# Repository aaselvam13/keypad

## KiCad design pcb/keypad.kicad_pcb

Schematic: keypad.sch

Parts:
C1, C2: 22pF; C_0805_2012Metric
C3, C4, C5: 0.1uF; C_0805_2012Metric
C6: 10uF; C_0805_2012Metric
C7: 1uF; C_0805_2012Metric
D1, D2, D3, D4, D5, D6: D_Small; D_SOD-123
F1: 500mA; Fuse_1206_3216Metric
MX1, MX2, MX3, MX4, MX5, MX6: MX-NoLED; MXOnly-1U-Hotswap
R1, R2: 22; R_0805_2012Metric
R3: 10k; R_0805_2012Metric
SW1: SW_Push; SKQG-1155865
U1: ATmega32U4-AU; TQFP-44_10x10mm_P0.8mm
USB1: Molex-0548190589
Y1: 16MHz; Crystal_SMD_3225-4Pin_3.2x2.5mm

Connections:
+5V: C3.1, C4.1, C5.1, C6.1, F1.1, U1.2 (UVCC), U1.7 (VBUS), U1.14 (VCC), U1.24 (AVCC), U1.34 (VCC), U1.44 (AVCC)
COL0: MX1.1 (COL), MX2.1 (COL), U1.29 (PB5)
COL1: MX3.1 (COL), MX4.1 (COL), U1.28 (PB4)
COL2: MX5.1 (COL), MX6.1 (COL), U1.26 (PD6)
D+: R2.2, USB1.3 (D+)
D-: R1.2, USB1.4 (D-)
GND: C1.2, C2.2, C3.2, C4.2, C5.2, C6.2, C7.2, R3.1, SW1.1, U1.5 (UGND), U1.15 (GND), U1.23 (GND), U1.35 (GND), U1.43 (GND), USB1.1 (GND), Y1.2, Y1.4
unnamed: C1.1, U1.16 (XTAL2), Y1.3
unnamed: C2.1, U1.17 (XTAL1), Y1.1
unnamed: C7.1, U1.6 (UCAP)
unnamed: D1.2, MX1.2 (ROW)
unnamed: D2.2, MX2.2 (ROW)
unnamed: D3.2, MX3.2 (ROW)
unnamed: D4.2, MX4.2 (ROW)
unnamed: D5.2, MX5.2 (ROW)
unnamed: D6.2, MX6.2 (ROW)
unnamed: R1.1, U1.3 (D-)
unnamed: R2.1, U1.4 (D+)
unnamed: R3.2, U1.33 (~HWB~/PE2)
unnamed: SW1.2, U1.13 (~RESET)
ROW0: D1.1, D3.1, D5.1, U1.27 (PD7)
ROW1: D2.1, D4.1, D6.1, U1.30 (PB6)
VCC: F1.2, USB1.5 (VBUS)

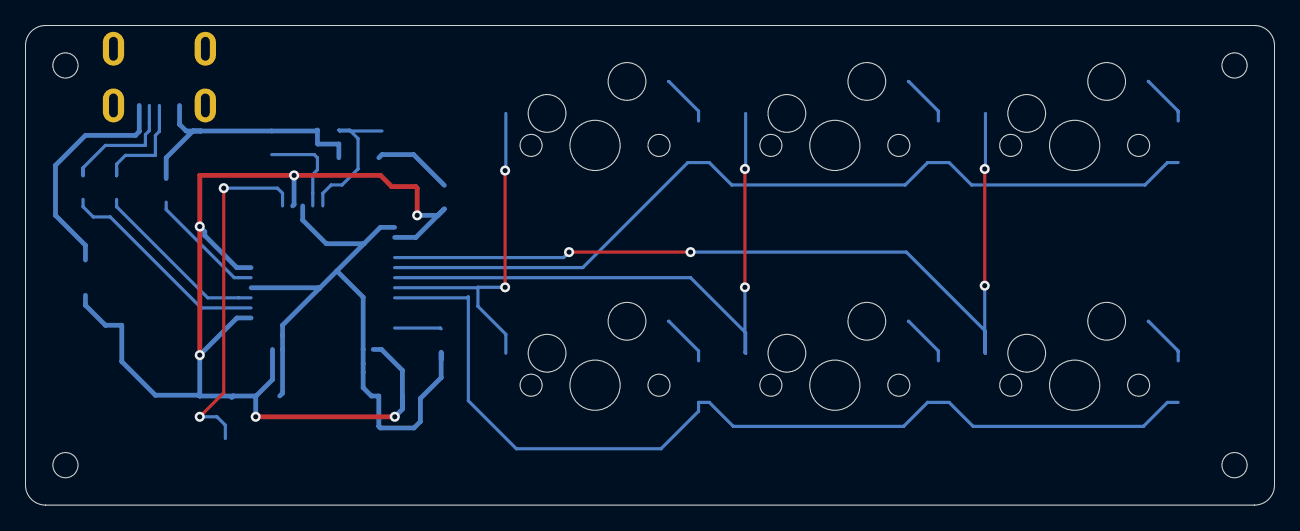
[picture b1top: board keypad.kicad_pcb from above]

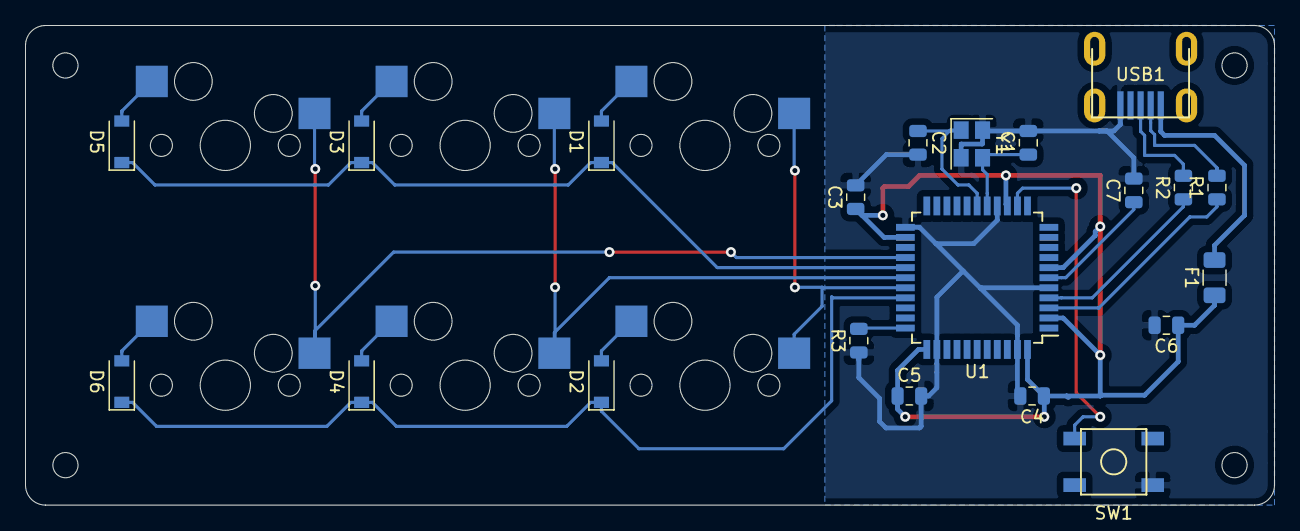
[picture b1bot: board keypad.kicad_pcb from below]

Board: 2 copper layers, 99.2 x 38.1 mm, 27 parts (21 on the bottom side), 23 nets.

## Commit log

2023-05-23 1
    initialize project files
2023-05-23 added submodules
    submodules
2023-05-23 edited libraries
    edited libraries
2023-05-23 MCU and USB
    both parts completed
2023-05-24 finished schematic
    done
2023-05-24 quick fix
    a
2023-05-24 footprints
    footprints done
2023-05-24 pcb update 1
    pcb!!
2023-05-24 routing
    first routing
2023-05-24 routing/fill
    complte
2023-05-28 holes + measurements
    e
2023-05-28 screws redone, switch moved
    e
2023-05-28 e
    e
2023-05-28 gerber + hole changes
    e
2023-05-28 gerbers and measurements
    a
2023-05-30 moved to pcb folder
    test
2023-05-30 new gerbers, removed hole
    e
2023-05-30 a
    a
2023-06-04 cad, pcb fixes
    a
2023-06-06 stuff
    stuff
2023-06-07 bruh
    bruh
2023-06-07 d
    d
2023-06-25 firmware
    firmware
2023-06-25 firmware 2
    firmware
